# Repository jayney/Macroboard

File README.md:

# Macroboard
20 Key Macro Keypad

An Arduino powered macro keyboard, designed for up to 20 x Cherry MX switches (or similar).The Arduino is a 5v 16MHz Sparkfun Pro Micro (32U4), or one of the cheap clones available on your favourite retail site!

Code is based on the Keypad library by Chris--A, and is available from the library manager in the Arduino IDE, or at

https://github.com/Chris--A/Keypad

The PCB is designed to fit Bopla BP810 enclosure.

Initially the keyboard strings attached to each key will need to be hard coded in the main loop. At some point I intend to put these into an #include file, and perhaps investigate upload and storage in EEPROM.

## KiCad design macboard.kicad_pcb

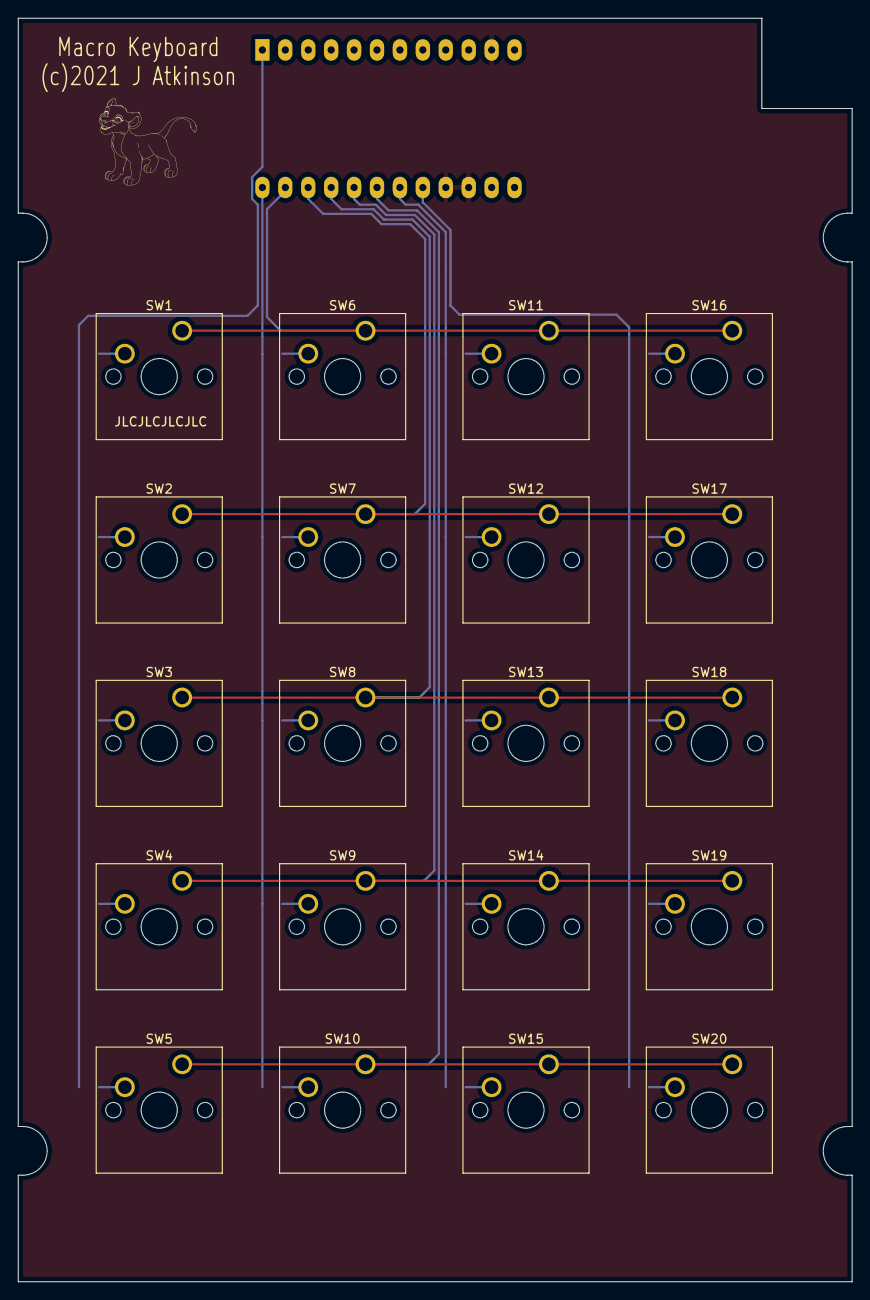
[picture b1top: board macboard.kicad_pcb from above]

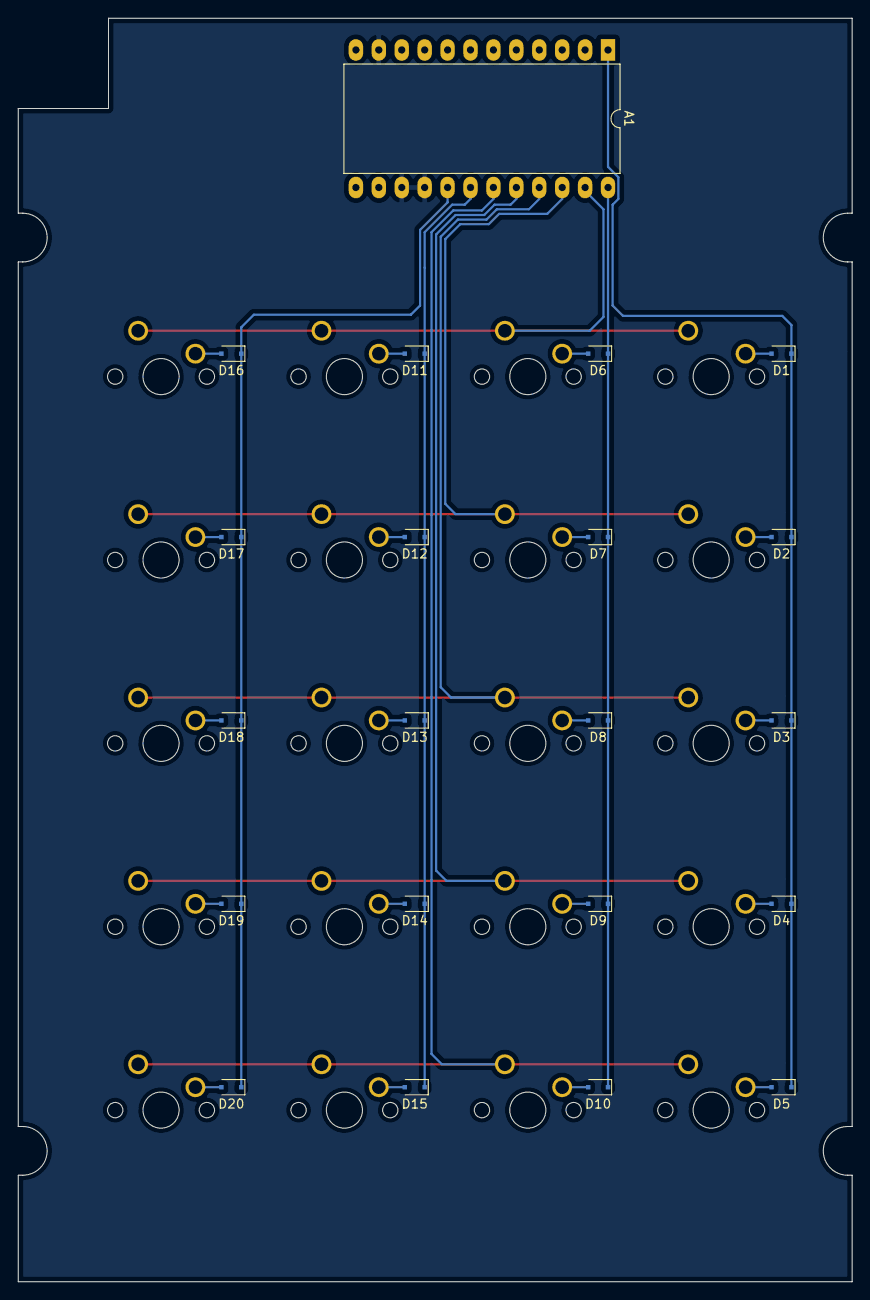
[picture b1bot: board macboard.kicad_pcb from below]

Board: 2 copper layers, 92.4 x 140.0 mm, 41 parts (21 on the bottom side), 30 nets.

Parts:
A1: Arduino_Pro_Micro; DIP-24_W15.24mm_LongPads
D1, D2, D3, D4, D5, D6, D7, D8, D9, D10, D11, D12, D13, D14, D15, D16, D17, D18, D19, D20: D; D_SOD-323F
SW1, SW2, SW3, SW4, SW5, SW6, SW7, SW8, SW9, SW10, SW11, SW12, SW13, SW14, SW15, SW16, SW17, SW18, SW19, SW20: SW_Push; SW_Cherry_MX_1.00u_PCB

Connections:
Col1: A1.1, D1.1, D2.1, D3.1, D4.1, D5.1
Col2: A1.24, D6.1, D7.1, D8.1, D9.1, D10.1
Col3: A1.18, D11.1, D12.1, D13.1, D14.1, D15.1
Col4: A1.17, D16.1, D17.1, D18.1, D19.1, D20.1
GND: A1.11, A1.15, A1.16
unnamed: D1.2, SW1.2
unnamed: D2.2, SW2.2
unnamed: D3.2, SW3.2
unnamed: D4.2, SW4.2
unnamed: D5.2, SW5.2
unnamed: D6.2, SW6.2
unnamed: D7.2, SW7.2
unnamed: D8.2, SW8.2
unnamed: D9.2, SW9.2
unnamed: D10.2, SW10.2
unnamed: D11.2, SW11.2
unnamed: D12.2, SW12.2
unnamed: D13.2, SW13.2
unnamed: D14.2, SW14.2
unnamed: D15.2, SW15.2
unnamed: D16.2, SW16.2
unnamed: D17.2, SW17.2
unnamed: D18.2, SW18.2
unnamed: D19.2, SW19.2
unnamed: D20.2, SW20.2
Row1: A1.23, SW1.1, SW6.1, SW11.1, SW16.1
Row2: A1.22, SW2.1, SW7.1, SW12.1, SW17.1
Row3: A1.21, SW3.1, SW8.1, SW13.1, SW18.1
Row4: A1.20, SW4.1, SW9.1, SW14.1, SW19.1
Row5: A1.19, SW5.1, SW10.1, SW15.1, SW20.1

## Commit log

2021-06-30 Create . ...
2021-06-30 Create x
2021-06-30 Basic Arduino Sketch

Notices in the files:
macboard.kicad_pcb:
(c)2021 J Atkinson
